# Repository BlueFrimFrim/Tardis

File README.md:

# Tardis_GIT

## DTMF
Uses MC8880C 20-pin DIP

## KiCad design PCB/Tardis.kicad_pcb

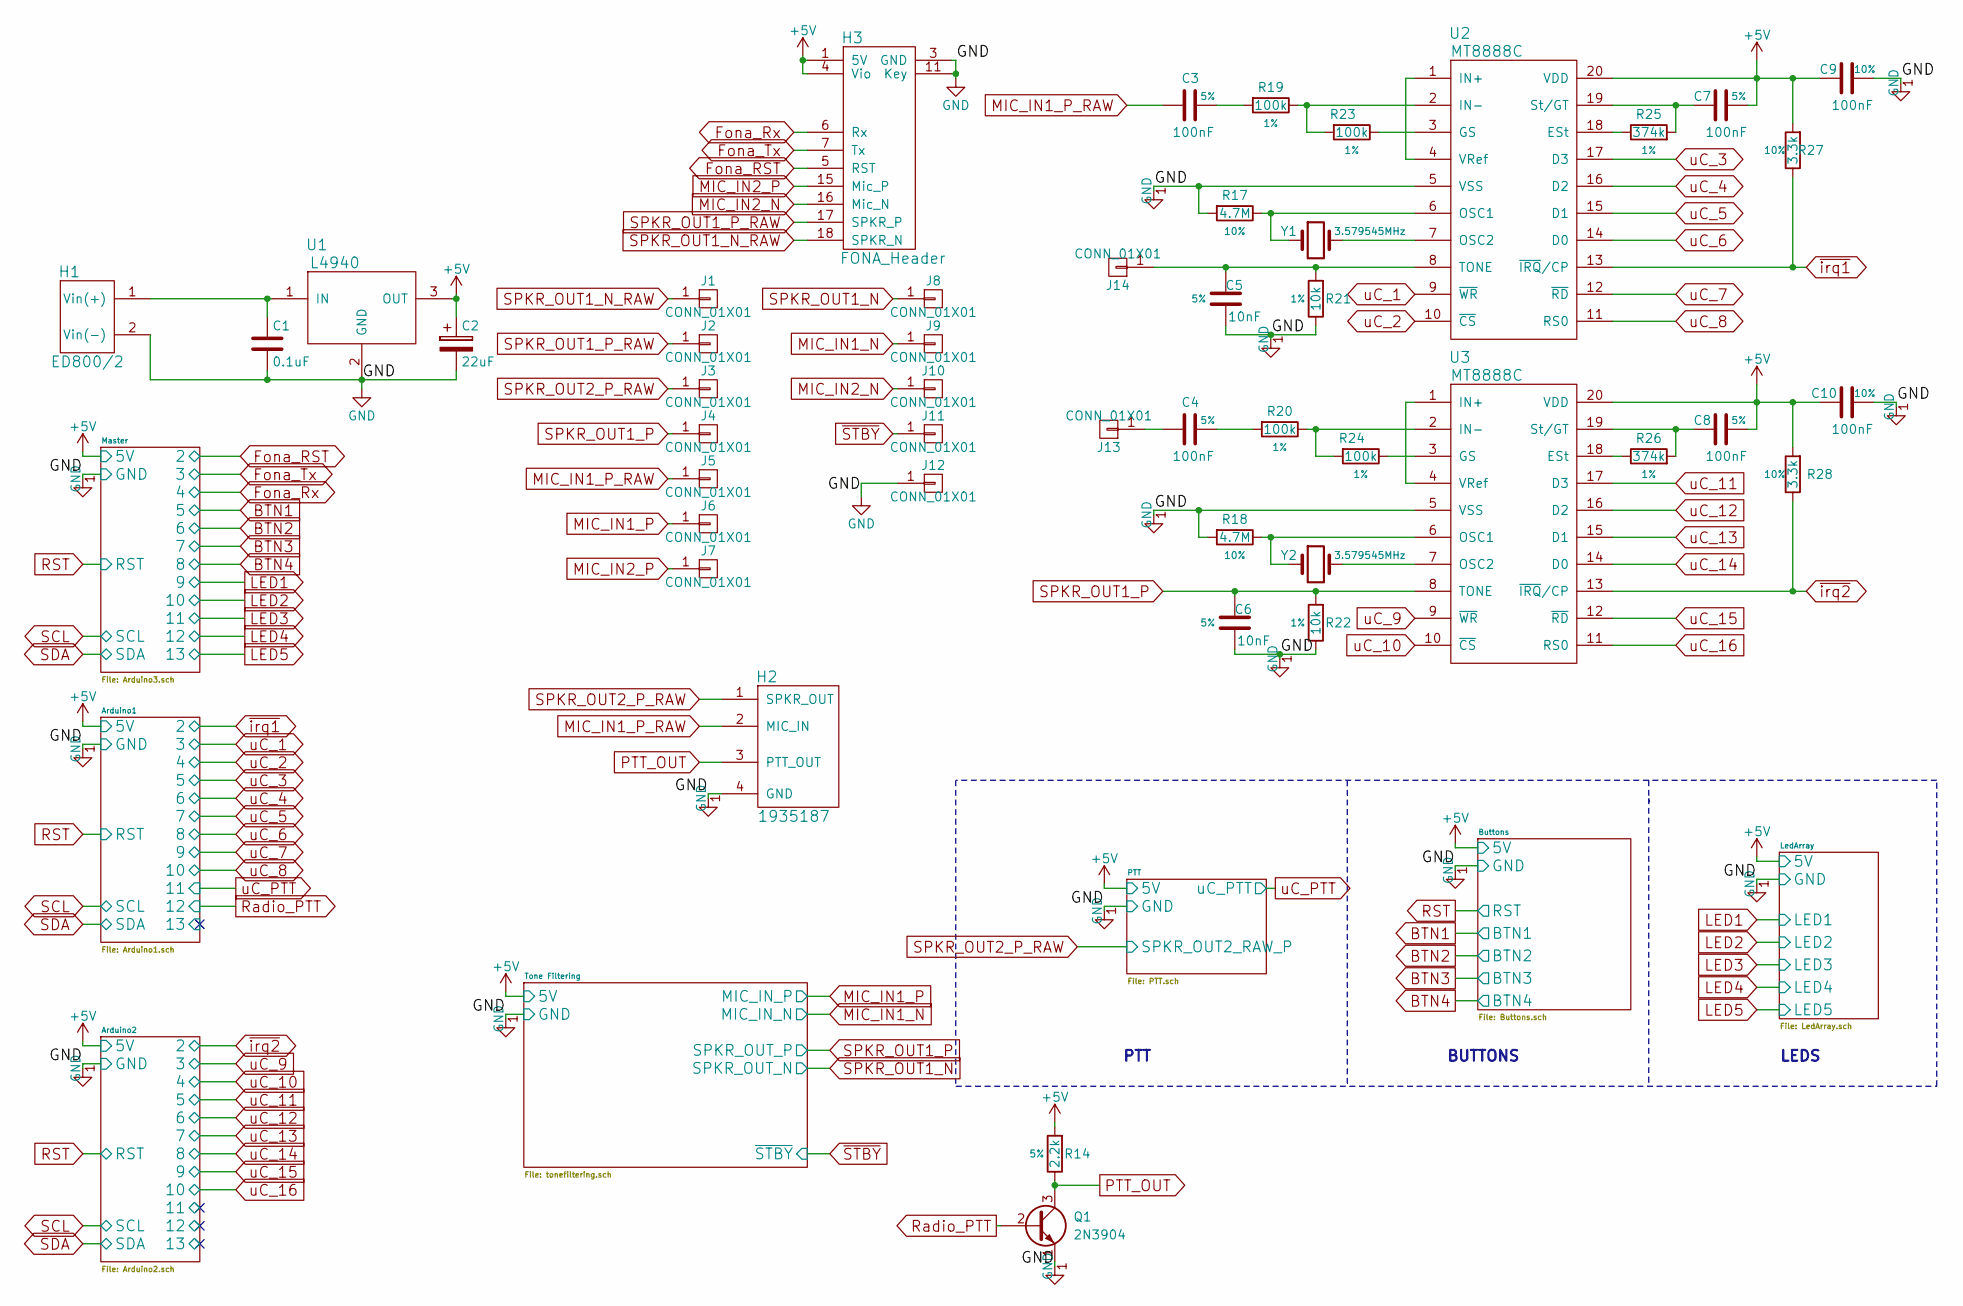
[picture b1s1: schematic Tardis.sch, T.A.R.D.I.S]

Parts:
C1: 0.1uF; C_0603_HandSoldering
C2: 22uF; RADIAL_5MM
C3, C4, C7, C8, C9, C10: 100nF; C_0603_HandSoldering
C5, C6: 10nF; C_0603_HandSoldering
H1: ED800/2; ED800
H2: 1935187
H3: FONA_Header; Pin_Header_Straight_1x18_Pitch2.54mm
J1, J2, J3, J4, J5, J6, J7, J8, J9, J10, J11, J12, J13, J14: CONN_01X01; Pin_Header_Straight_1x01_Pitch2.54mm
Q1: 2N3904; TO-92_Molded_Narrow
R14: 2.2k; R_0603_HandSoldering
R17, R18: 4.7M; R_0603_HandSoldering
R19, R20, R23, R24: 100k; R_0603_HandSoldering
R21, R22: 10k; R_0603_HandSoldering
R25, R26: 374k; R_0603_HandSoldering
R27, R28: 3.3k; R_0603_HandSoldering
U1: L4940; TO-220-3_Horizontal
U2, U3: MT8888C; SOIC-20
Y1, Y2: 3.579545MHz; Crystal_SMD_HC49-SD_HandSoldering

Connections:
+5V: C2.1, C7.2, C8.2, C9.1, C10.1, H3.1 (5V), H3.4 (Vio), R14.2, R27.2, R28.2, U1.3 (OUT), U2.20 (VDD), U3.20 (VDD); also elsewhere on the board
/GND: C1.2, C2.2, C5.1, C6.1, C9.2, C10.2, H1.2 (Vin(-)), H2.4 (GND), H3.3 (GND), H3.11 (Key), J12.1, Q1.1 (E), R17.2, R18.2, R21.1, R22.1, U1.2 (GND), U2.5 (VSS), U3.5 (VSS); also elsewhere on the board
Fona_RST: H3.5 (RST); also elsewhere on the board
Fona_Rx: H3.6 (Rx); also elsewhere on the board
Fona_Tx: H3.7 (Tx); also elsewhere on the board
MIC_IN1_N: J9.1; also elsewhere on the board
MIC_IN1_P: J6.1; also elsewhere on the board
MIC_IN1_P_RAW: C3.2, H2.2 (MIC_IN), J5.1
MIC_IN2_N: H3.16 (Mic_N), J10.1
MIC_IN2_P: H3.15 (Mic_P), J7.1
unnamed: C1.1, H1.1 (Vin(+)), U1.1 (IN)
unnamed: C3.1, R19.2
unnamed: C4.1, R20.2
unnamed: C4.2, J13.1
unnamed: C5.2, J14.1, R21.2, U2.8 (TONE)
unnamed: C7.1, R25.2, U2.19 (St/GT)
unnamed: C8.1, R26.2, U3.19 (St/GT)
unnamed: R17.1, U2.6 (OSC1), Y1.1
unnamed: R18.1, U3.6 (OSC1), Y2.1
unnamed: R19.1, R23.2, U2.2 (IN-)
unnamed: R20.1, R24.2, U3.2 (IN-)
unnamed: R23.1, U2.3 (GS)
unnamed: R24.1, U3.3 (GS)
unnamed: R25.1, U2.18 (ESt)
unnamed: R26.1, U3.18 (ESt)
unnamed: U2.1 (IN+), U2.4 (VRef)
unnamed: U2.7 (OSC2), Y1.2
unnamed: U3.1 (IN+), U3.4 (VRef)
unnamed: U3.7 (OSC2), Y2.2
PTT_OUT: H2.3 (PTT_OUT), Q1.3 (C), R14.1
Radio_PTT: Q1.2 (B); also elsewhere on the board
SPKR_OUT1_N: J8.1; also elsewhere on the board
SPKR_OUT1_N_RAW: H3.18 (SPKR_N), J1.1
SPKR_OUT1_P: C6.2, J4.1, R22.2, U3.8 (TONE); also elsewhere on the board
SPKR_OUT1_P_RAW: H3.17 (SPKR_P), J2.1
SPKR_OUT2_P_RAW: H2.1 (SPKR_OUT), J3.1; also elsewhere on the board
uC_1: U2.9 (~WR); also elsewhere on the board
uC_2: U2.10 (~CS); also elsewhere on the board
uC_3: U2.17 (D3); also elsewhere on the board
uC_4: U2.16 (D2); also elsewhere on the board
uC_5: U2.15 (D1); also elsewhere on the board
uC_6: U2.14 (D0); also elsewhere on the board
uC_7: U2.12 (~RD); also elsewhere on the board
uC_8: U2.11 (RS0); also elsewhere on the board
uC_9: U3.9 (~WR); also elsewhere on the board
uC_10: U3.10 (~CS); also elsewhere on the board
uC_11: U3.17 (D3); also elsewhere on the board
uC_12: U3.16 (D2); also elsewhere on the board
uC_13: U3.15 (D1); also elsewhere on the board
uC_14: U3.14 (D0); also elsewhere on the board
uC_15: U3.12 (~RD); also elsewhere on the board
uC_16: U3.11 (RS0); also elsewhere on the board
~STBY: J11.1; also elsewhere on the board
~irq1: R27.1, U2.13 (~IRQ~/CP); also elsewhere on the board
~irq2: R28.1, U3.13 (~IRQ~/CP); also elsewhere on the board

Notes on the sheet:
LEDS
BUTTONS
PTT

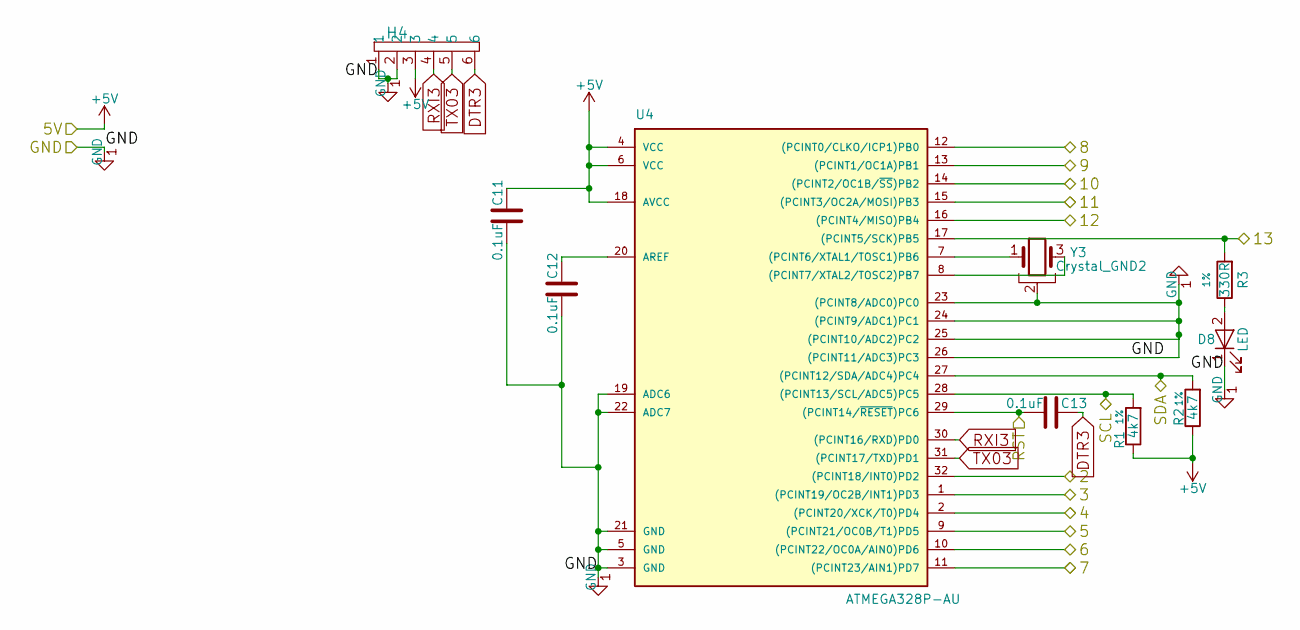
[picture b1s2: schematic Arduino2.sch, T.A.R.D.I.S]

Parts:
C11, C12, C13: 0.1uF; C_0603_HandSoldering
D8: LED; LED_0805_HandSoldering
H4: Header1; Pin_Header_Straight_1x06_Pitch2.54mm
R1, R2: 4k7; R_0603_HandSoldering
R3: 330R; R_0603_HandSoldering
U4: ATMEGA328P-AU; TQFP-32_7x7mm_Pitch0.8mm
Y3: Crystal_GND2; Resonator_SMD-3pin_7.2x3.0mm_HandSoldering

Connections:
+5V: C11.1, H4.3, R1.1, R2.1, U4.4 (VCC), U4.6 (VCC), U4.18 (AVCC); also elsewhere on the board
/Arduino2/11: U4.15 ((PCINT3/OC2A/MOSI)PB3)
/Arduino2/12: U4.16 ((PCINT4/MISO)PB4)
/Arduino2/13: R3.2, U4.17 ((PCINT5/SCK)PB5)
/GND: C11.2, C12.2, D8.1 (K), H4.1, H4.2, U4.3 (GND), U4.5 (GND), U4.19 (ADC6), U4.21 (GND), U4.22 (ADC7), U4.23 ((PCINT8/ADC0)PC0), U4.24 ((PCINT9/ADC1)PC1), U4.25 ((PCINT10/ADC2)PC2), U4.26 ((PCINT11/ADC3)PC3), Y3.2; also elsewhere on the board
DTR3: C13.1, H4.6
unnamed: C12.1, U4.20 (AREF)
unnamed: D8.2 (A), R3.1
unnamed: U4.7 ((PCINT6/XTAL1/TOSC1)PB6), Y3.1
unnamed: U4.8 ((PCINT7/XTAL2/TOSC2)PB7), Y3.3
RST: C13.2, U4.29 ((PCINT14/~RESET~)PC6); also elsewhere on the board
RXI3: H4.4, U4.30 ((PCINT16/RXD)PD0)
SCL: R1.2, U4.28 ((PCINT13/SCL/ADC5)PC5); also elsewhere on the board
SDA: R2.2, U4.27 ((PCINT12/SDA/ADC4)PC4); also elsewhere on the board
TX03: H4.5, U4.31 ((PCINT17/TXD)PD1)
uC_9: U4.1 ((PCINT19/OC2B/INT1)PD3); also elsewhere on the board
uC_10: U4.2 ((PCINT20/XCK/T0)PD4); also elsewhere on the board
uC_11: U4.9 ((PCINT21/OC0B/T1)PD5); also elsewhere on the board
uC_12: U4.10 ((PCINT22/OC0A/AIN0)PD6); also elsewhere on the board
uC_13: U4.11 ((PCINT23/AIN1)PD7); also elsewhere on the board
uC_14: U4.12 ((PCINT0/CLKO/ICP1)PB0); also elsewhere on the board
uC_15: U4.13 ((PCINT1/OC1A)PB1); also elsewhere on the board
uC_16: U4.14 ((PCINT2/OC1B/~SS~)PB2); also elsewhere on the board
~irq2: U4.32 ((PCINT18/INT0)PD2); also elsewhere on the board

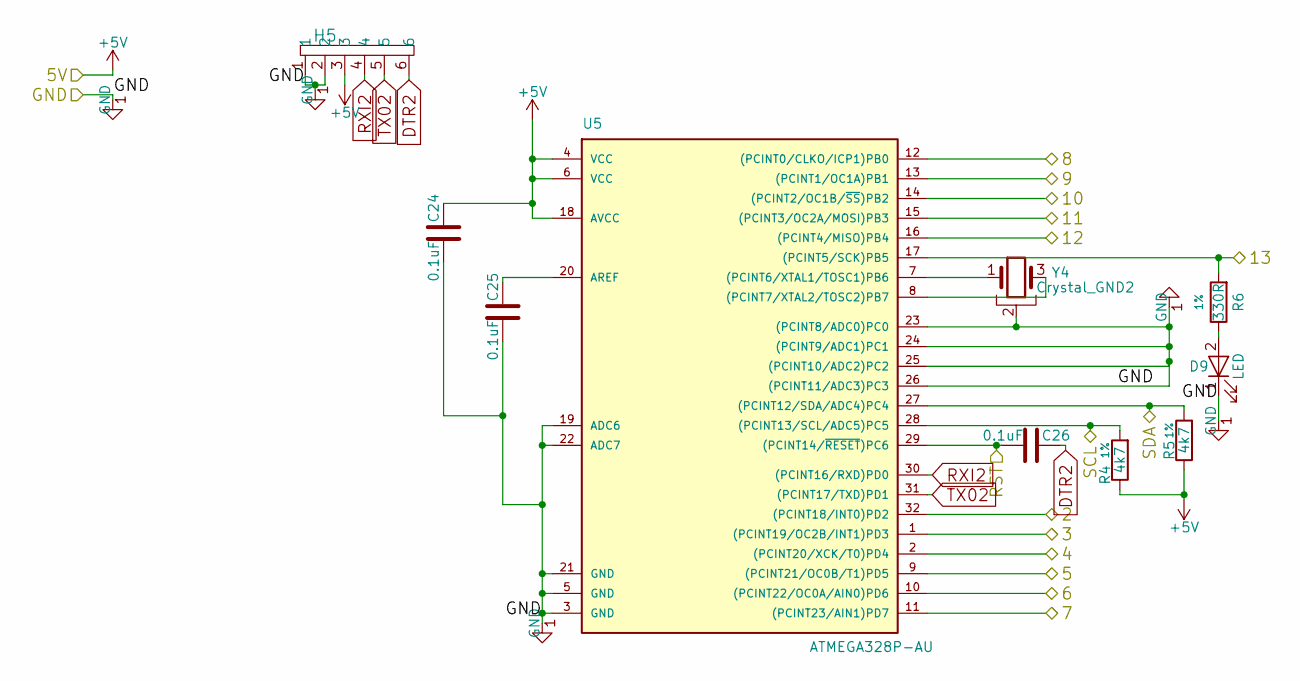
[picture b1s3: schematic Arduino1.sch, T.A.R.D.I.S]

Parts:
C24, C25, C26: 0.1uF; C_0603_HandSoldering
D9: LED; LED_0805_HandSoldering
H5: Header1; Pin_Header_Straight_1x06_Pitch2.54mm
R4, R5: 4k7; R_0603_HandSoldering
R6: 330R; R_0603_HandSoldering
U5: ATMEGA328P-AU; TQFP-32_7x7mm_Pitch0.8mm
Y4: Crystal_GND2; Resonator_SMD-3pin_7.2x3.0mm_HandSoldering

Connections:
+5V: C24.1, H5.3, R4.1, R5.1, U5.4 (VCC), U5.6 (VCC), U5.18 (AVCC); also elsewhere on the board
/Arduino1/13: R6.2, U5.17 ((PCINT5/SCK)PB5)
/GND: C24.2, C25.2, D9.1 (K), H5.1, H5.2, U5.3 (GND), U5.5 (GND), U5.19 (ADC6), U5.21 (GND), U5.22 (ADC7), U5.23 ((PCINT8/ADC0)PC0), U5.24 ((PCINT9/ADC1)PC1), U5.25 ((PCINT10/ADC2)PC2), U5.26 ((PCINT11/ADC3)PC3), Y4.2; also elsewhere on the board
DTR2: C26.1, H5.6
unnamed: C25.1, U5.20 (AREF)
unnamed: D9.2 (A), R6.1
unnamed: U5.7 ((PCINT6/XTAL1/TOSC1)PB6), Y4.1
unnamed: U5.8 ((PCINT7/XTAL2/TOSC2)PB7), Y4.3
RST: C26.2, U5.29 ((PCINT14/~RESET~)PC6); also elsewhere on the board
RXI2: H5.4, U5.30 ((PCINT16/RXD)PD0)
Radio_PTT: U5.16 ((PCINT4/MISO)PB4); also elsewhere on the board
SCL: R4.2, U5.28 ((PCINT13/SCL/ADC5)PC5); also elsewhere on the board
SDA: R5.2, U5.27 ((PCINT12/SDA/ADC4)PC4); also elsewhere on the board
TX02: H5.5, U5.31 ((PCINT17/TXD)PD1)
uC_1: U5.1 ((PCINT19/OC2B/INT1)PD3); also elsewhere on the board
uC_2: U5.2 ((PCINT20/XCK/T0)PD4); also elsewhere on the board
uC_3: U5.9 ((PCINT21/OC0B/T1)PD5); also elsewhere on the board
uC_4: U5.10 ((PCINT22/OC0A/AIN0)PD6); also elsewhere on the board
uC_5: U5.11 ((PCINT23/AIN1)PD7); also elsewhere on the board
uC_6: U5.12 ((PCINT0/CLKO/ICP1)PB0); also elsewhere on the board
uC_7: U5.13 ((PCINT1/OC1A)PB1); also elsewhere on the board
uC_8: U5.14 ((PCINT2/OC1B/~SS~)PB2); also elsewhere on the board
uC_PTT: U5.15 ((PCINT3/OC2A/MOSI)PB3); also elsewhere on the board
~irq1: U5.32 ((PCINT18/INT0)PD2); also elsewhere on the board

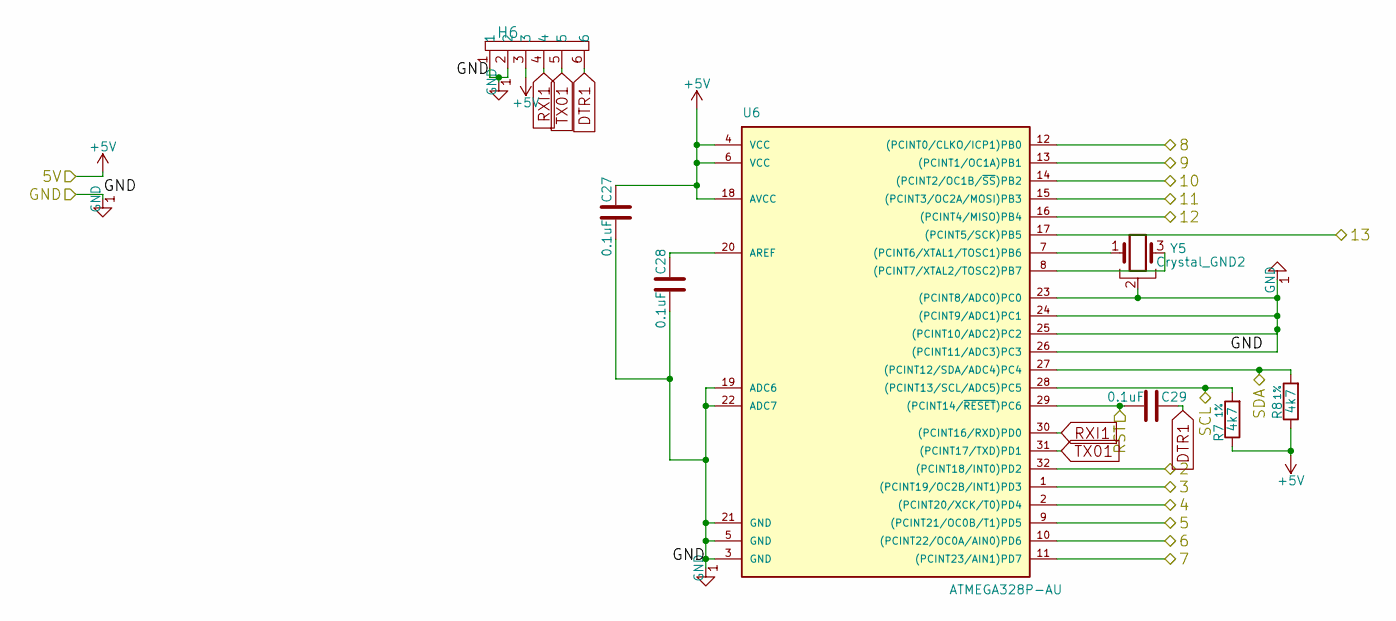
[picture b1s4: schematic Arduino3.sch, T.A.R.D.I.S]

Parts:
C27, C28, C29: 0.1uF; C_0603_HandSoldering
H6: Header1; Pin_Header_Straight_1x06_Pitch2.54mm
R7, R8: 4k7; R_0603_HandSoldering
U6: ATMEGA328P-AU; TQFP-32_7x7mm_Pitch0.8mm
Y5: Crystal_GND2; Resonator_SMD-3pin_7.2x3.0mm_HandSoldering

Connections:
+5V: C27.1, H6.3, R7.1, R8.1, U6.4 (VCC), U6.6 (VCC), U6.18 (AVCC); also elsewhere on the board
/GND: C27.2, C28.2, H6.1, H6.2, U6.3 (GND), U6.5 (GND), U6.19 (ADC6), U6.21 (GND), U6.22 (ADC7), U6.23 ((PCINT8/ADC0)PC0), U6.24 ((PCINT9/ADC1)PC1), U6.25 ((PCINT10/ADC2)PC2), U6.26 ((PCINT11/ADC3)PC3), Y5.2; also elsewhere on the board
BTN1: U6.9 ((PCINT21/OC0B/T1)PD5); also elsewhere on the board
BTN2: U6.10 ((PCINT22/OC0A/AIN0)PD6); also elsewhere on the board
BTN3: U6.11 ((PCINT23/AIN1)PD7); also elsewhere on the board
BTN4: U6.12 ((PCINT0/CLKO/ICP1)PB0); also elsewhere on the board
DTR1: C29.1, H6.6
Fona_RST: U6.32 ((PCINT18/INT0)PD2); also elsewhere on the board
Fona_Rx: U6.2 ((PCINT20/XCK/T0)PD4); also elsewhere on the board
Fona_Tx: U6.1 ((PCINT19/OC2B/INT1)PD3); also elsewhere on the board
LED1: U6.13 ((PCINT1/OC1A)PB1); also elsewhere on the board
LED2: U6.14 ((PCINT2/OC1B/~SS~)PB2); also elsewhere on the board
LED3: U6.15 ((PCINT3/OC2A/MOSI)PB3); also elsewhere on the board
LED4: U6.16 ((PCINT4/MISO)PB4); also elsewhere on the board
LED5: U6.17 ((PCINT5/SCK)PB5); also elsewhere on the board
unnamed: C28.1, U6.20 (AREF)
unnamed: U6.7 ((PCINT6/XTAL1/TOSC1)PB6), Y5.1
unnamed: U6.8 ((PCINT7/XTAL2/TOSC2)PB7), Y5.3
RST: C29.2, U6.29 ((PCINT14/~RESET~)PC6); also elsewhere on the board
RXI1: H6.4, U6.30 ((PCINT16/RXD)PD0)
SCL: R7.2, U6.28 ((PCINT13/SCL/ADC5)PC5); also elsewhere on the board
SDA: R8.2, U6.27 ((PCINT12/SDA/ADC4)PC4); also elsewhere on the board
TX01: H6.5, U6.31 ((PCINT17/TXD)PD1)

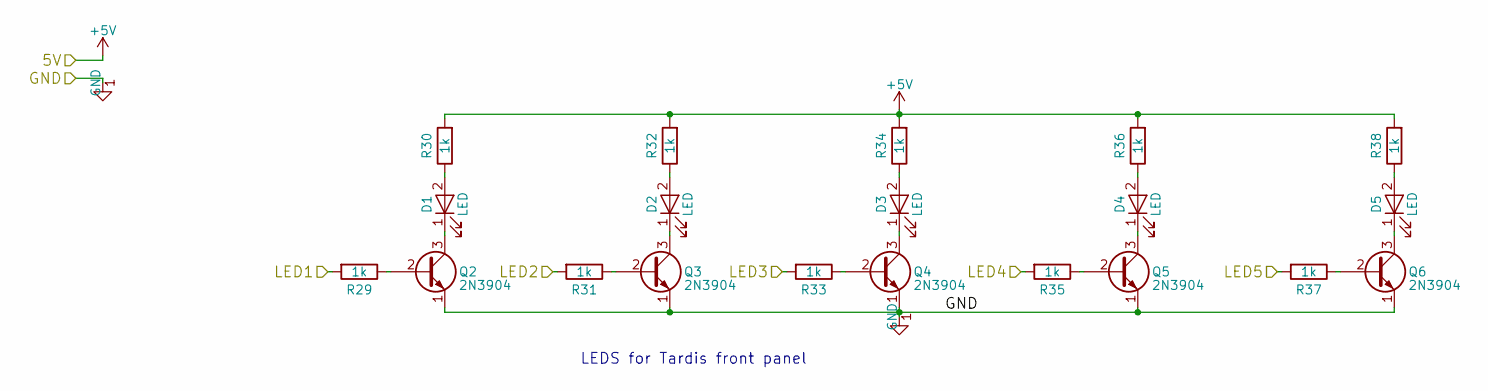
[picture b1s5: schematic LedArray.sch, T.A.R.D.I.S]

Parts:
D1, D2, D3, D4, D5: LED; LED_D5.0mm
Q2, Q3, Q4, Q5, Q6: 2N3904; TO-92_Molded_Narrow
R29, R30, R31, R32, R33, R34, R35, R36, R37, R38: 1k; R_0603_HandSoldering

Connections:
+5V: R30.2, R32.2, R34.2, R36.2, R38.2; also elsewhere on the board
/GND: Q2.1 (E), Q3.1 (E), Q4.1 (E), Q5.1 (E), Q6.1 (E); also elsewhere on the board
LED1: R29.2; also elsewhere on the board
LED2: R31.2; also elsewhere on the board
LED3: R33.2; also elsewhere on the board
LED4: R35.2; also elsewhere on the board
LED5: R37.2; also elsewhere on the board
unnamed: D1.1 (K), Q2.3 (C)
unnamed: D1.2 (A), R30.1
unnamed: D2.1 (K), Q3.3 (C)
unnamed: D2.2 (A), R32.1
unnamed: D3.1 (K), Q4.3 (C)
unnamed: D3.2 (A), R34.1
unnamed: D4.1 (K), Q5.3 (C)
unnamed: D4.2 (A), R36.1
unnamed: D5.1 (K), Q6.3 (C)
unnamed: D5.2 (A), R38.1
unnamed: Q2.2 (B), R29.1
unnamed: Q3.2 (B), R31.1
unnamed: Q4.2 (B), R33.1
unnamed: Q5.2 (B), R35.1
unnamed: Q6.2 (B), R37.1

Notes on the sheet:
LEDS for Tardis front panel

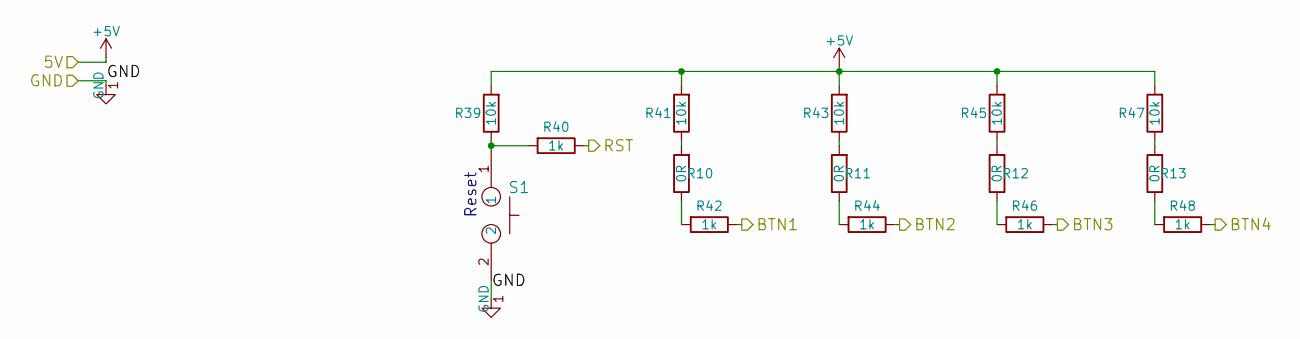
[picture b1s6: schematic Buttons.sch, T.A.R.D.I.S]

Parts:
R10, R11, R12, R13: 0R; R_Axial_DIN0204_L3.6mm_D1.6mm_P2.54mm_Vertical
R39, R41, R43, R45, R47: 10k; R_0603_HandSoldering
R40, R42, R44, R46, R48: 1k; R_0603_HandSoldering
S1: mom_button; SW_TH_Tactile_Omron_B3F-10xx

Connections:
+5V: R39.2, R41.2, R43.2, R45.2, R47.2; also elsewhere on the board
/GND: S1.2; also elsewhere on the board
BTN1: R42.1; also elsewhere on the board
BTN2: R44.1; also elsewhere on the board
BTN3: R46.1; also elsewhere on the board
BTN4: R48.1; also elsewhere on the board
unnamed: R10.1, R42.2
unnamed: R10.2, R41.1
unnamed: R11.1, R44.2
unnamed: R11.2, R43.1
unnamed: R12.1, R46.2
unnamed: R12.2, R45.1
unnamed: R13.1, R48.2
unnamed: R13.2, R47.1
unnamed: R39.1, R40.2, S1.1
RST: R40.1; also elsewhere on the board

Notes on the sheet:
Reset

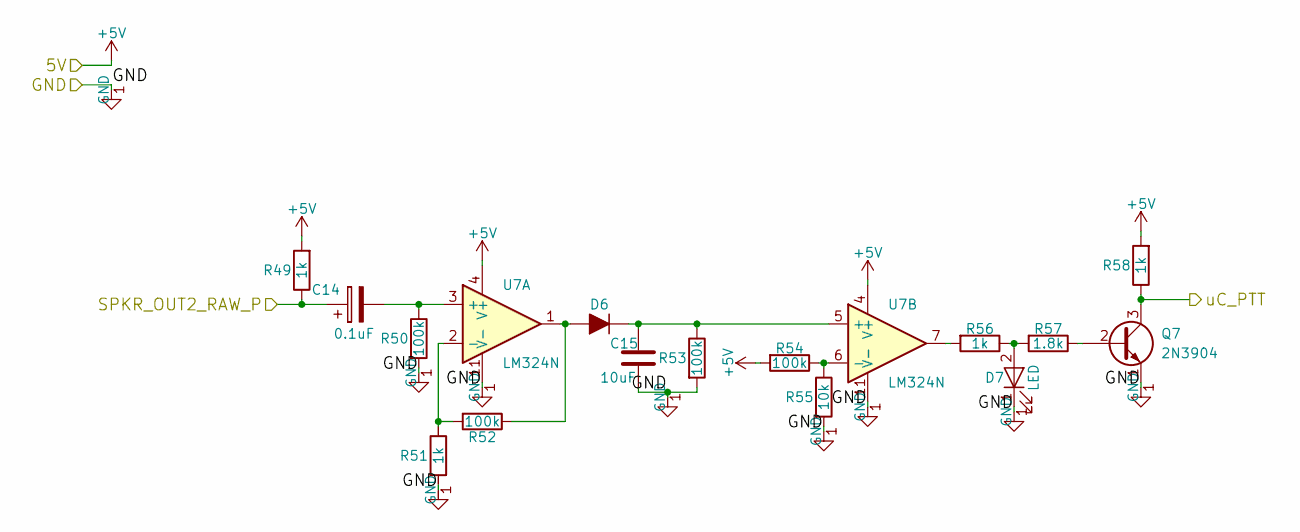
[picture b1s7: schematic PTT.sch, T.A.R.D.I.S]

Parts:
C14: 0.1uF; CP_Radial_D5.0mm_P2.00mm
C15: 10uF; C_0603_HandSoldering
D6: D_ALT; D_SOD-323_HandSoldering
D7: LED; LED_0805_HandSoldering
Q7: 2N3904; TO-92_Molded_Narrow
R49, R51, R56, R58: 1k; R_0603_HandSoldering
R50, R52, R53, R54: 100k; R_0603_HandSoldering
R55: 10k; R_0603_HandSoldering
R57: 1.8k; R_0603_HandSoldering
U7: LM324N; SOIC-14_N

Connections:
+5V: R49.2, R54.2, R58.2, U7.4 (V+); also elsewhere on the board
/GND: C15.2, D7.1 (K), Q7.1 (E), R50.2, R51.2, R53.2, R55.2, U7.11 (V-); also elsewhere on the board
unnamed: C14.2, R50.1, U7.3 (+)
unnamed: C15.1, D6.1 (K), R53.1, U7.5 (+)
unnamed: D6.2 (A), R52.1, U7.1
unnamed: D7.2 (A), R56.1, R57.2
unnamed: Q7.2 (B), R57.1
unnamed: R51.1, R52.2, U7.2 (-)
unnamed: R54.1, R55.1, U7.6 (-)
unnamed: R56.2, U7.7
SPKR_OUT2_P_RAW: C14.1, R49.1; also elsewhere on the board
uC_PTT: Q7.3 (C), R58.1; also elsewhere on the board

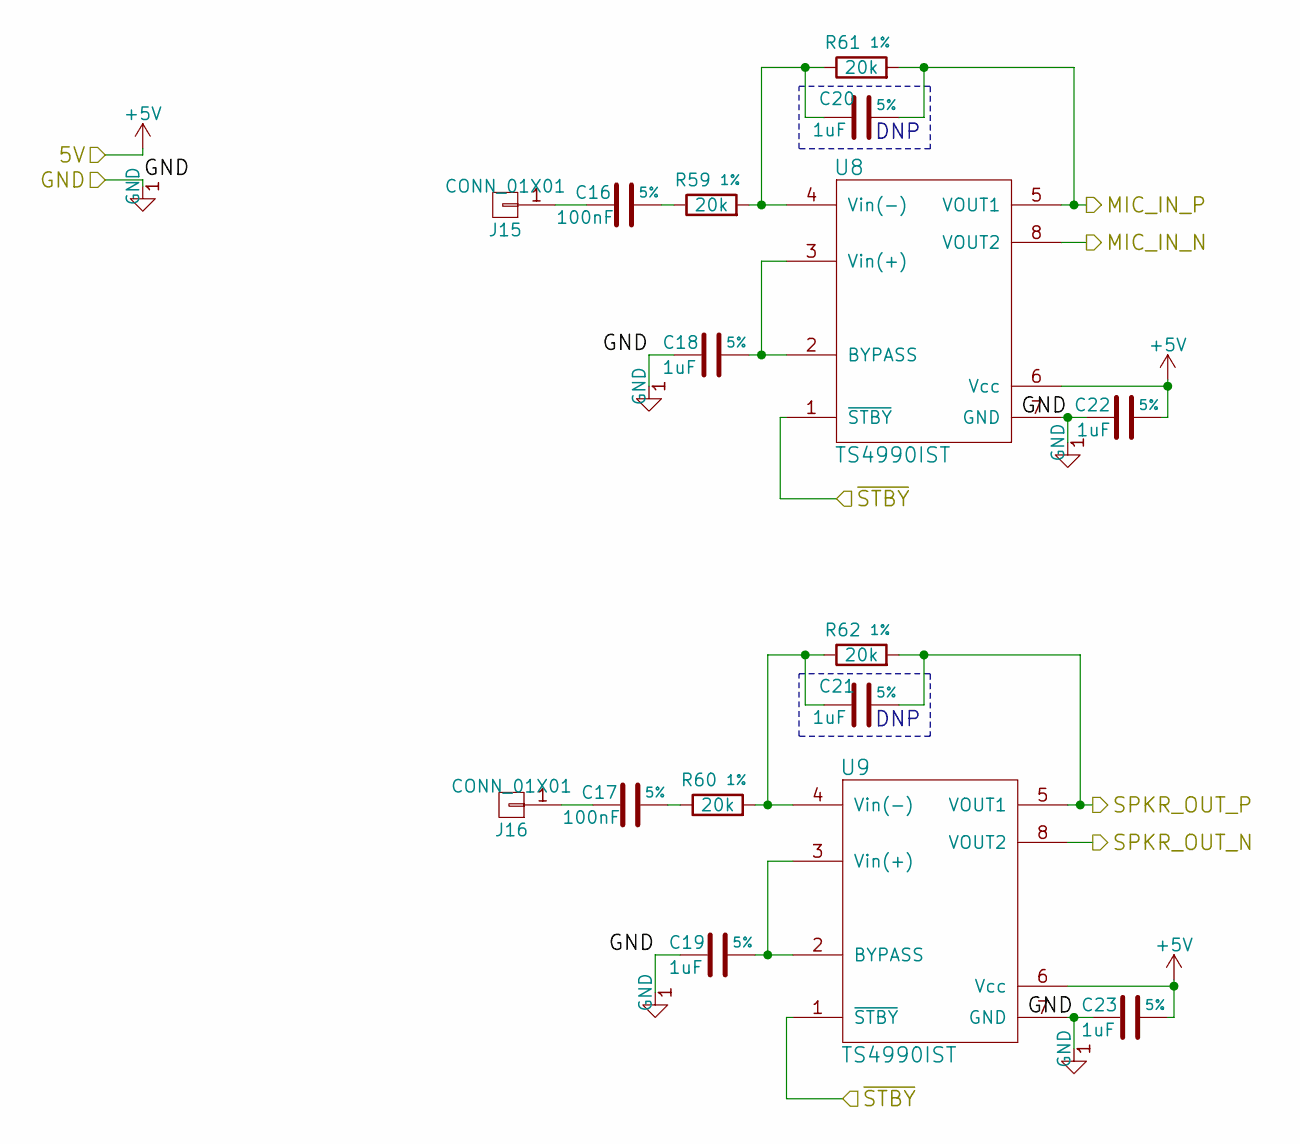
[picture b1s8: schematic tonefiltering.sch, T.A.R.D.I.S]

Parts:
C16, C17: 100nF; C_0603_HandSoldering
C18, C19, C20, C21, C22, C23: 1uF; C_0603_HandSoldering
J15, J16: CONN_01X01; Pin_Header_Straight_1x01_Pitch2.54mm
R59, R60, R61, R62: 20k; R_0603_HandSoldering
U8, U9: TS4990IST; MSOP-8_3x3mm_Pitch0.65mm

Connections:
+5V: C22.2, C23.1, U8.6 (Vcc), U9.6 (Vcc); also elsewhere on the board
/GND: C18.2, C19.2, C22.1, C23.2, U8.7 (GND), U9.7 (GND); also elsewhere on the board
MIC_IN1_N: U8.8 (VOUT2); also elsewhere on the board
MIC_IN1_P: C20.1, R61.2, U8.5 (VOUT1); also elsewhere on the board
unnamed: C16.1, R59.1
unnamed: C16.2, J15.1
unnamed: C17.1, R60.1
unnamed: C17.2, J16.1
unnamed: C18.1, U8.2 (BYPASS), U8.3 (Vin(+))
unnamed: C19.1, U9.2 (BYPASS), U9.3 (Vin(+))
unnamed: C20.2, R59.2, R61.1, U8.4 (Vin(-))
unnamed: C21.2, R60.2, R62.1, U9.4 (Vin(-))
SPKR_OUT1_N: U9.8 (VOUT2); also elsewhere on the board
SPKR_OUT1_P: C21.1, R62.2, U9.5 (VOUT1); also elsewhere on the board
~STBY: U8.1 (~STBY), U9.1 (~STBY); also elsewhere on the board

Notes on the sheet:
DNP

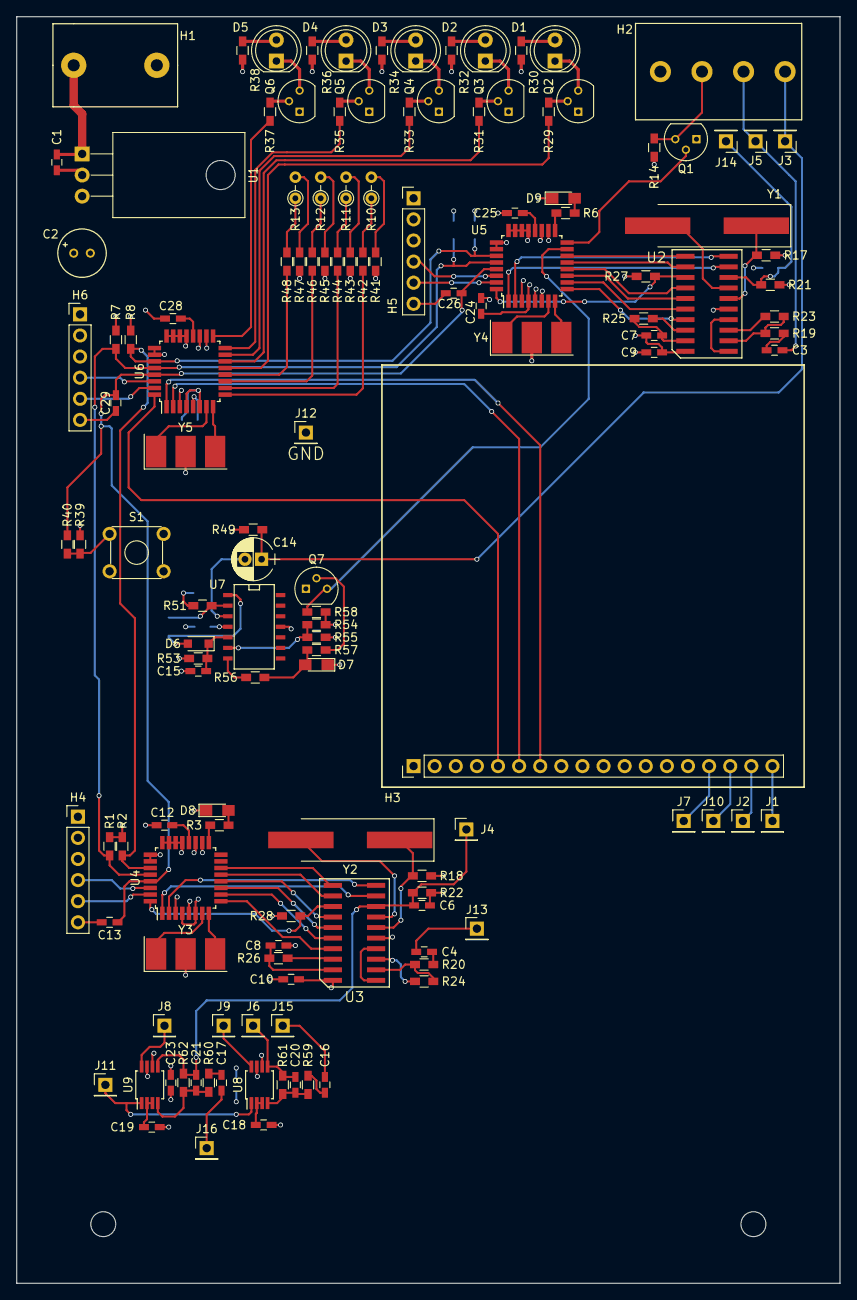
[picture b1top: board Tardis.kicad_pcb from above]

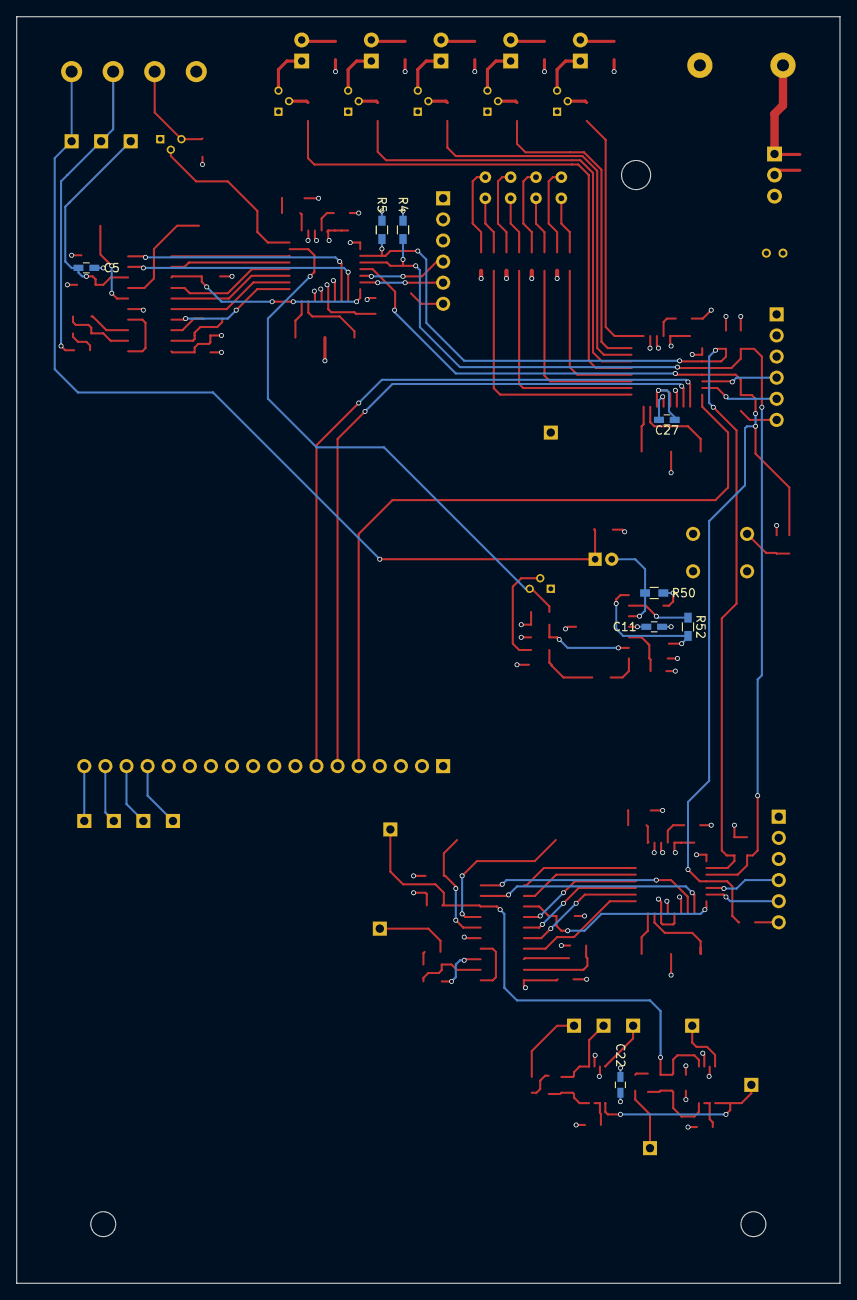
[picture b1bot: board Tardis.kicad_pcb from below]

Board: 4 copper layers, 99.1 x 152.4 mm, 141 parts (8 on the bottom side), 130 nets.

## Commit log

2016-11-26 Created tardis.ino
2016-11-26 Put tardis.ino in it's own folder so ArduinoIDE will be able torecognize it.
2016-11-27 Started tardis.ino
2016-11-27 Added chipset to ReadMe
2016-11-27 created libraries folder
2016-11-30 added PIC folder
2016-11-30 removed microchip folder
2016-12-01 created knight rider function
2016-12-04 Converted Diego's code. Not 100%, not working
2016-12-04 C:/Program Files/Git
2016-12-18 added library, and gcc_test
2017-01-19 removed pic and useless libraries
2017-01-19 added tardis_phone.ino
2017-01-19 converting code
2017-01-22 converted C++ to Tardis C
2017-01-22 Code works
2017-01-25 arduino interrupts work.
2017-01-25 Interrupts work, receiving works.
2017-01-26 moved tardis_phone.ino into it's own folder
2017-02-20 bug: interrupt hung when using serial
2017-02-20 Split up two main functions
2017-04-19 Added Doc folder
2017-05-22 added 'mainframe' folder for stm32 mbed
2017-05-24 added steps to dial phone number instead of having preset numbers
2017-05-29 TODO: Remove extern 'C' wrapers
2017-05-30 added Visual Studio Arduino project
2017-05-30 dtmf.cpp/h compiles. NOT TESTED
2017-06-01 Re-write/cleanup compiles. NOT TESTED
2017-06-03 Tested, runs. Interrupts are a bit iffy.
2017-06-03 Added libraries for 7-segment display
2017-06-04 Receive compiles.
2017-06-13 See notes.
2017-06-13 Saved project
2017-06-14 dtmf.cpp/h are pretty much complete
2017-06-14 Formatted Log.md
2017-06-20 see Log.md
2017-06-20 moved files into 'includes' and 'lib'
2017-06-22 see Log
2017-06-22 added irq and receive_avr.h
2017-07-12 added working revision of Tardis ino
2017-07-14 added timeout.cpp/h
2017-07-14 See log for changes
2017-07-21 commented out dtmf, tested 5 minute timer
2017-07-26 added two commands
2017-07-28 made globals volatile
2017-08-06 added dave project for ptt
2017-08-07 added PTT_OUT
2017-08-09 added Cellular_AVR
2017-08-20 revised Receive
2017-08-21 added test folder
2017-08-21 answer/hangup work
2017-08-22 5 second timer works
2017-08-24 30 minute timer works
2017-09-03 added MCP23S17 library
2017-09-04 io expander doesn't work
2017-12-10 Added test comment for GitKraken
2017-12-10 Added KiCad PCB Files
2017-12-12 Added jumpers to bypass amp
2017-12-16 Adding footprints
2017-12-17 Adding footprints cont.
2018-01-12 Added PCB layout
2018-01-14 PCB Done. To be reviewed.
2018-01-14 Added gerbers.
2018-01-18 added 0.15inch clearance to edges
2018-01-21 new gerbers
2018-06-15 Removed Raycast, implemented spawning bullets.
2018-06-28 Invoices added
2018-06-28 Adding button/led functionality
